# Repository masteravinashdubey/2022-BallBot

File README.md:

<a href="https://www.youtube.com/watch?v=X55rTUPi5_A&list=PLK0jpMYIBd6BGnQJQYf43Kv_qziwwk5SU&index=11"># 50_Banti_Pai_Robot</a>

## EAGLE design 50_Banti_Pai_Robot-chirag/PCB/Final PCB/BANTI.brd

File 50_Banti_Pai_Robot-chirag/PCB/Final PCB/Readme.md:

This is a modification of the bantipai_bottom. In this there are slots and one mounting screw-hole for each of the four [motor driver](http://www.nex-robotics.com/products/motor-drivers/dc-motor-drivers/hercules-series-motor-drivers/hercules-lite-6v-36v-8amp-motor-driver.html)\
In this, the motor drivers are situated at right angles to each other and equidistant to the eyfi-mega, which is placed at the center.
However, since this PCB is compact, the motor driver is won't be completely inside the board, some part of it would be peeking outside, and thus it is imperative to make
additional changes(mounting holes) on the acrylic sheet on which the PCB is to be mounted.

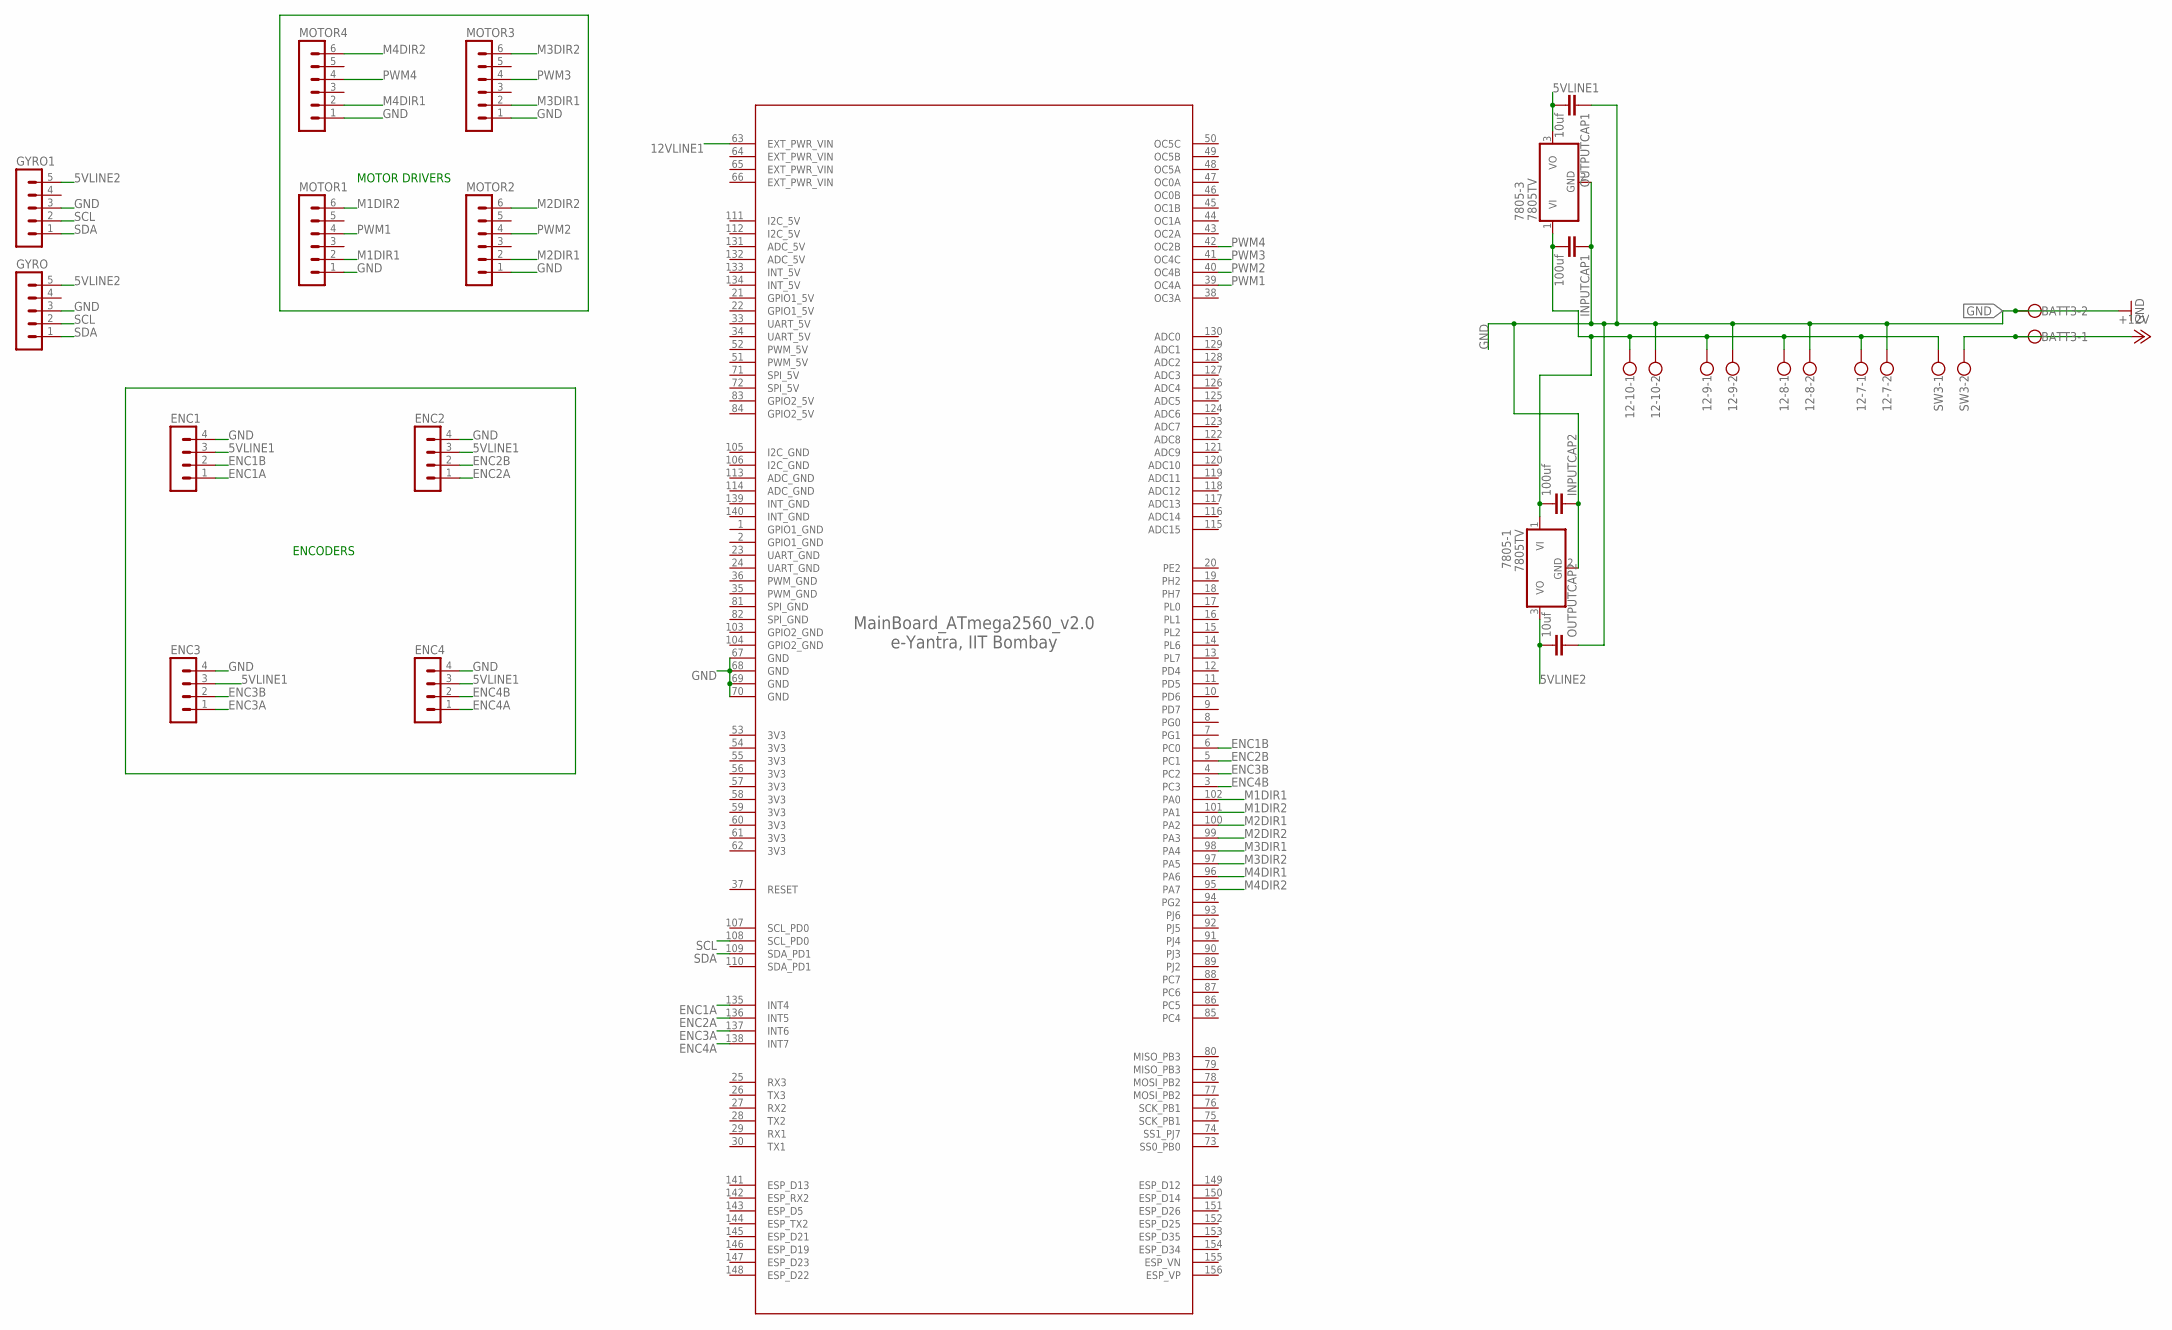
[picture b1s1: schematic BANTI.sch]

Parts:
12-7, 12-8, 12-9, 12-10: W237-102
7805-1, 7805-3: 7805TV; TO220V
BATT3: W237-102
ENC1, ENC2, ENC3, ENC4: MA04-1
EYFI: ATMEGA2560_V2.0
GYRO, GYRO1: MA05-1
INPUTCAP1, INPUTCAP2: 100uf; C2.5-2
MOTOR1, MOTOR2, MOTOR3, MOTOR4: MA06-1
OUTPUTCAP1, OUTPUTCAP2: 10uf; C2.5-2
SW3: W237-102

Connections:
3V3: EYFI.53 (3V3), EYFI.54 (3V3), EYFI.55 (3V3), EYFI.56 (3V3), EYFI.57 (3V3), EYFI.58 (3V3), EYFI.59 (3V3), EYFI.60 (3V3), EYFI.61 (3V3), EYFI.62 (3V3)
5VLINE1: 7805-3.3 (VO), ENC1.3, ENC2.3, ENC3.3, ENC4.3, OUTPUTCAP1.2
5VLINE2: 7805-1.3 (VO), GYRO.5, GYRO1.5, OUTPUTCAP2.2
12VLINE1: 12-7.1, 12-8.1, 12-9.1, 12-10.1, 7805-1.1 (VI), 7805-3.1 (VI), EYFI.63 (EXT_PWR_VIN), INPUTCAP1.2, INPUTCAP2.2, SW3.1
+12V: BATT3.1, SW3.2
ADC_5V: EYFI.131 (ADC_5V), EYFI.132 (ADC_5V)
ADC_GND: EYFI.113 (ADC_GND), EYFI.114 (ADC_GND)
ENC1A: ENC1.1, EYFI.135 (INT4)
ENC1B: ENC1.2, EYFI.6 (PC0)
ENC2A: ENC2.1, EYFI.136 (INT5)
ENC2B: ENC2.2, EYFI.5 (PC1)
ENC3A: ENC3.1, EYFI.137 (INT6)
ENC3B: ENC3.2, EYFI.4 (PC2)
ENC4A: ENC4.1, EYFI.138 (INT7)
ENC4B: ENC4.2, EYFI.3 (PC3)
EXT_PWR_VIN: EYFI.64 (EXT_PWR_VIN), EYFI.65 (EXT_PWR_VIN), EYFI.66 (EXT_PWR_VIN)
GND: 12-7.2, 12-8.2, 12-9.2, 12-10.2, 7805-1.2 (GND), 7805-3.2 (GND), BATT3.2, ENC1.4, ENC2.4, ENC3.4, ENC4.4, EYFI.67 (GND), EYFI.68 (GND), EYFI.69 (GND), EYFI.70 (GND), GYRO.3, GYRO1.3, INPUTCAP1.1, INPUTCAP2.1, MOTOR1.1, MOTOR2.1, MOTOR3.1, MOTOR4.1, OUTPUTCAP1.1, OUTPUTCAP2.1
GPIO1_5V: EYFI.21 (GPIO1_5V), EYFI.22 (GPIO1_5V)
GPIO1_GND: EYFI.1 (GPIO1_GND), EYFI.2 (GPIO1_GND)
GPIO2_5V: EYFI.83 (GPIO2_5V), EYFI.84 (GPIO2_5V)
GPIO2_GND: EYFI.103 (GPIO2_GND), EYFI.104 (GPIO2_GND)
I2C_5V: EYFI.111 (I2C_5V), EYFI.112 (I2C_5V)
I2C_GND: EYFI.105 (I2C_GND), EYFI.106 (I2C_GND)
INT_5V: EYFI.133 (INT_5V), EYFI.134 (INT_5V)
INT_GND: EYFI.139 (INT_GND), EYFI.140 (INT_GND)
M1DIR1: EYFI.102 (PA0), MOTOR1.2
M1DIR2: EYFI.101 (PA1), MOTOR1.6
M2DIR1: EYFI.100 (PA2), MOTOR2.2
M2DIR2: EYFI.99 (PA3), MOTOR2.6
M3DIR1: EYFI.98 (PA4), MOTOR3.2
M3DIR2: EYFI.97 (PA5), MOTOR3.6
M4DIR1: EYFI.96 (PA6), MOTOR4.2
M4DIR2: EYFI.95 (PA7), MOTOR4.6
PWM1: EYFI.39 (OC4A), MOTOR1.4
PWM2: EYFI.40 (OC4B), MOTOR2.4
PWM3: EYFI.41 (OC4C), MOTOR3.4
PWM4: EYFI.42 (OC2B), MOTOR4.4
PWM_5V: EYFI.51 (PWM_5V), EYFI.52 (PWM_5V)
PWM_GND: EYFI.35 (PWM_GND), EYFI.36 (PWM_GND)
SCL: EYFI.108 (SCL_PD0), GYRO.2, GYRO1.2
SDA: EYFI.109 (SDA_PD1), GYRO.1, GYRO1.1
SPI_5V: EYFI.71 (SPI_5V), EYFI.72 (SPI_5V)
SPI_GND: EYFI.81 (SPI_GND), EYFI.82 (SPI_GND)
UART_5V: EYFI.33 (UART_5V), EYFI.34 (UART_5V)
UART_GND: EYFI.23 (UART_GND), EYFI.24 (UART_GND)

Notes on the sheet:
ENCODERS
MOTOR DRIVERS

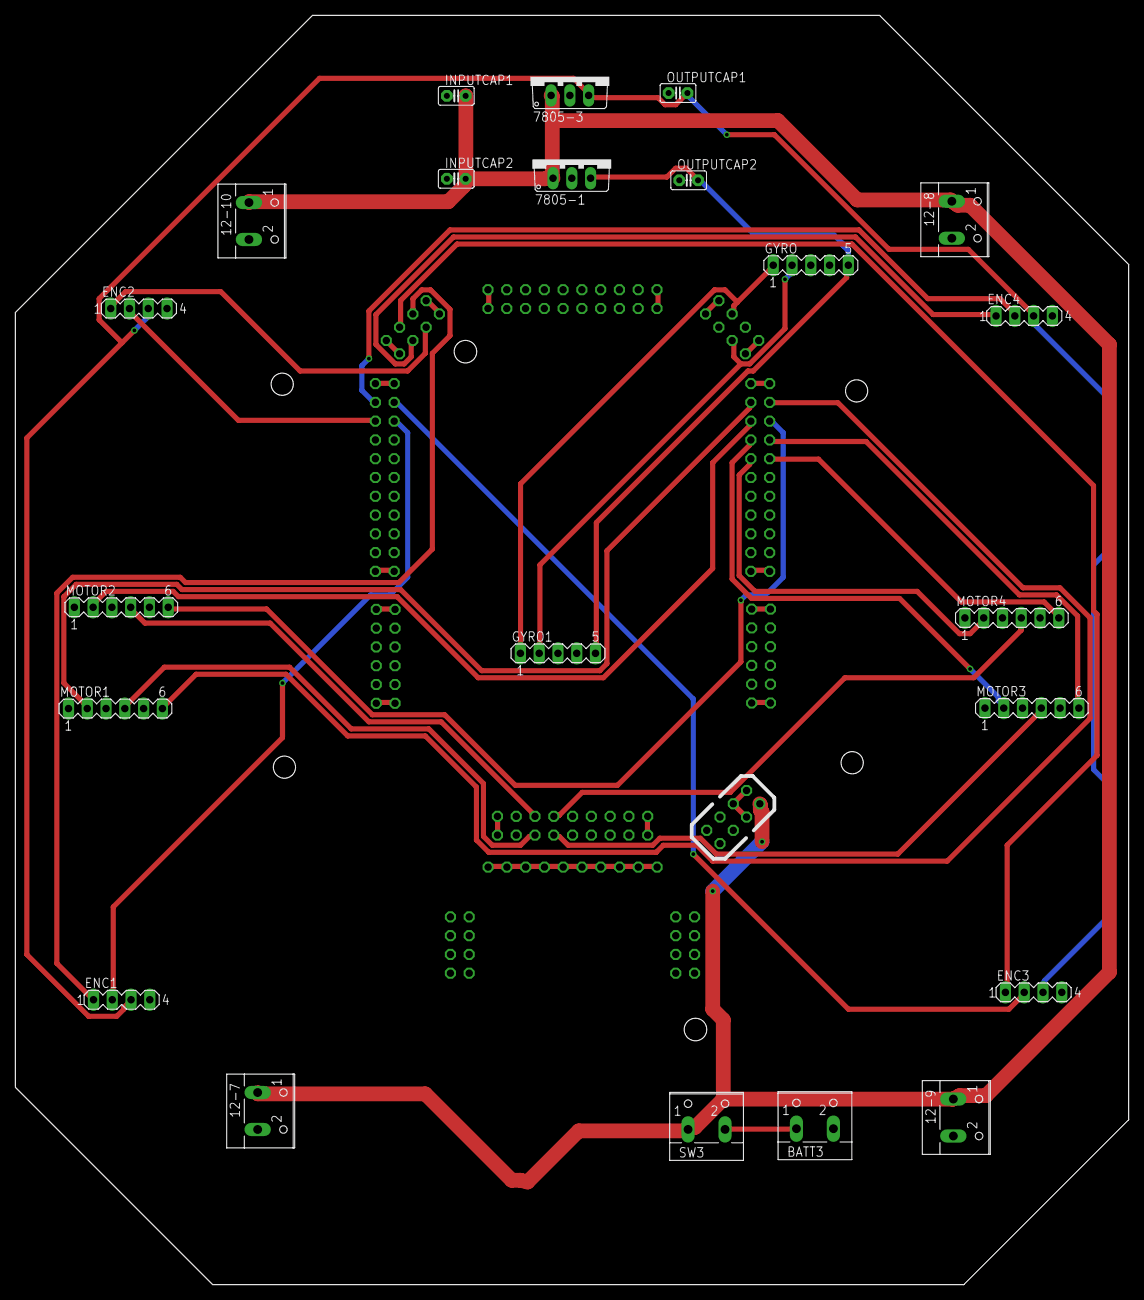
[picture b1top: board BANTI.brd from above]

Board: 2 copper layers, 150.6 x 171.7 mm, 23 parts (0 on the bottom side), 45 nets.

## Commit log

2023-12-04 Swarit Files
2023-12-04 chirag files
